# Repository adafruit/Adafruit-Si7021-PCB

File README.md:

## Adafruit Si7021 Temperature & Humidity Sensor Breakout PCB
<a href="http://www.adafruit.com/products/3251"><br/>
Click here to purchase one from the Adafruit shop</a>

It's summer and you're sweating and your hair's all frizzy and all you really want to know is why the weatherman said this morning that today's relative humidity would max out at a perfectly reasonable 42% when it feels more like 77%. Enter the Si7021 Temperature + Humidity Sensor - the best way to prove the weatherman wrong!

This lovely sensor for Silicon labs has ± 3% relative humidity measurements with a range of 0–80% RH, and ±0.4 °C temperature accuracy at a range of -10 to +85 °C. Great for all of your environmental sensing projects. It uses I2C for data transfer so it works with a wide range of microcontrollers.

To get you going fast, we spun up a custom made PCB in the STEMMA QT form factor, making them easy to interface with. The STEMMA QT connectors on either side are compatible with the SparkFun Qwiic I2C connectors. This allows you to make solderless connections between your development board and the LIS331s or to chain them with a wide range of other sensors and accessories using a compatible cable. We’ve of course broken out all the pins to standard headers and added a voltage regulator and level shifting so allow you to use it with either 3.3V or 5V systems such as the Raspberry Pi + Feather series or Arduino Uno respectively.

PCB files for the Adafruit Si7021 PCB. The format is EagleCAD schematic and board layout
- https://www.adafruit.com/products/3251

### License

Adafruit invests time and resources providing this open source design, please support Adafruit and open-source hardware by purchasing products from [Adafruit](https://www.adafruit.com)!

All text above must be included in any redistribution

Designed by Limor Fried/Ladyada for Adafruit Industries.
Creative Commons Attribution/Share-Alike, all text above must be included in any redistribution. 
See license.txt for additional information.

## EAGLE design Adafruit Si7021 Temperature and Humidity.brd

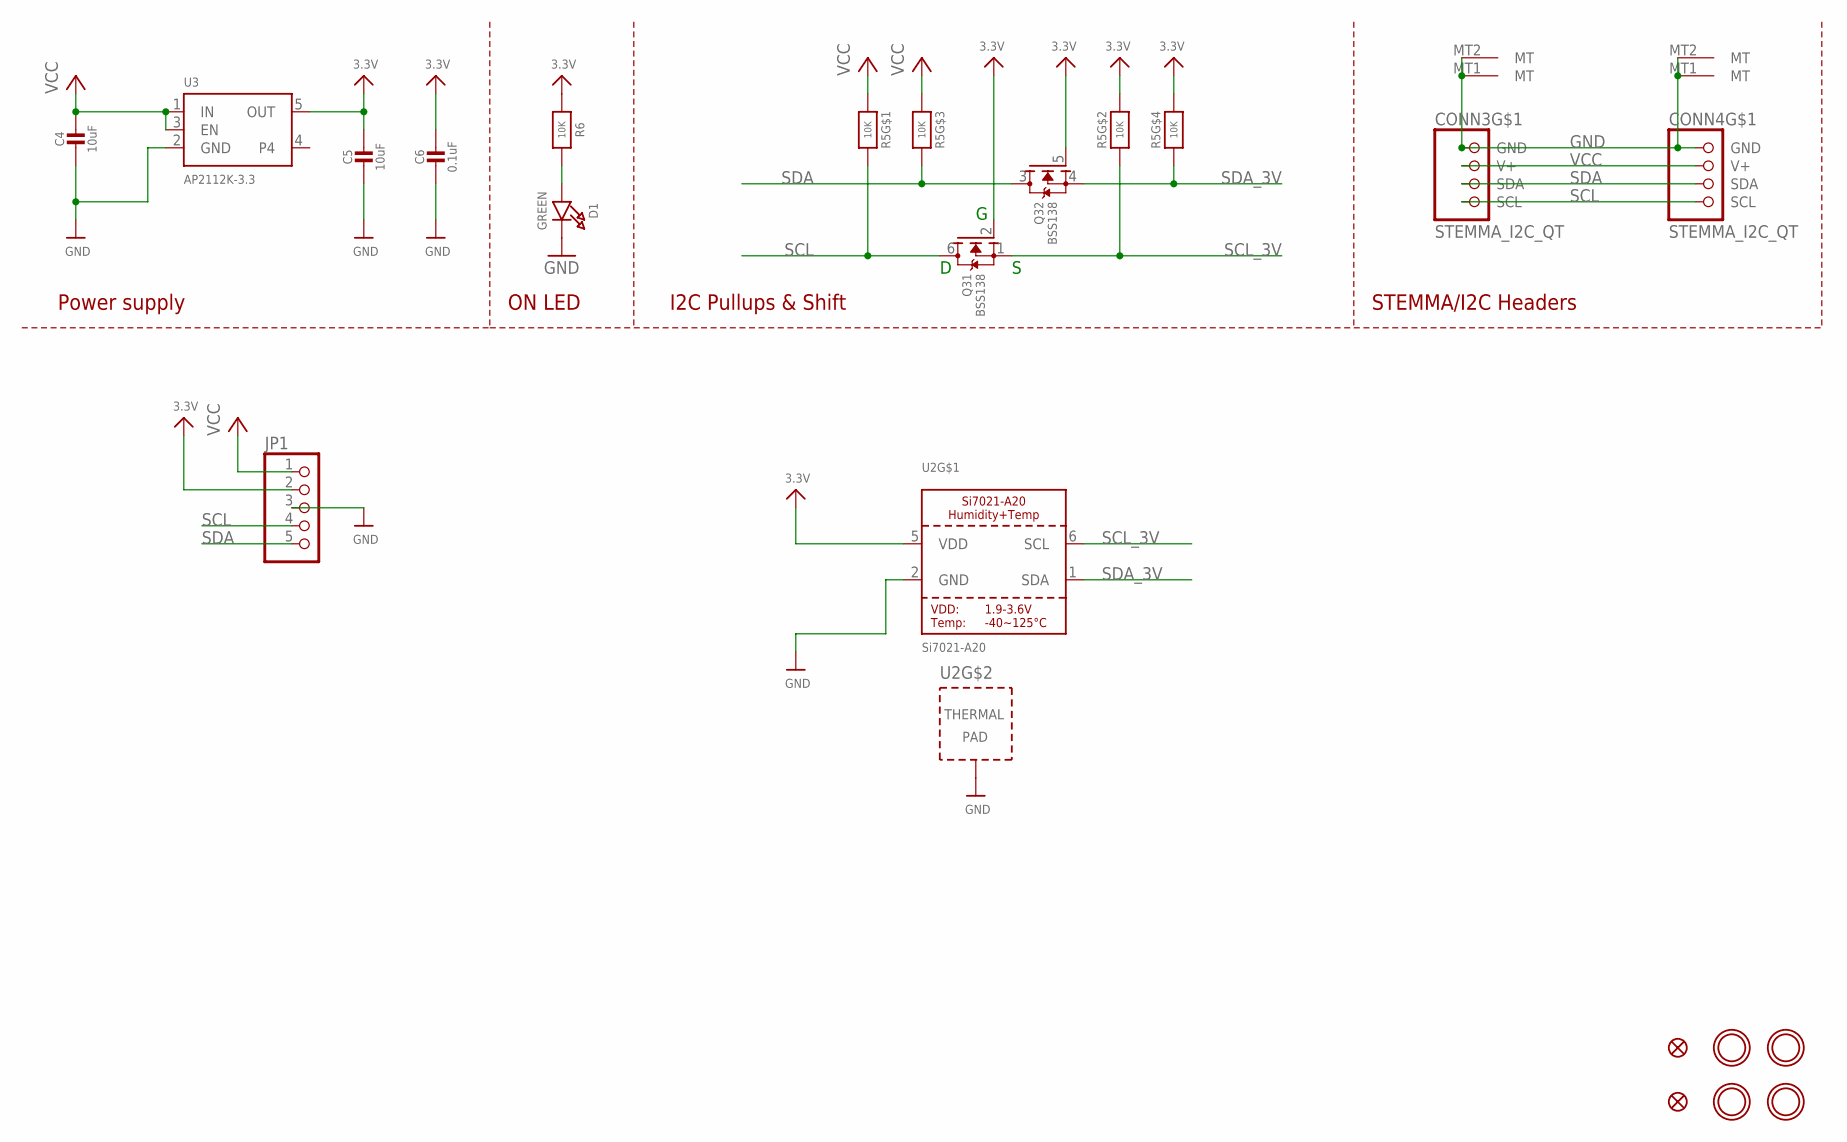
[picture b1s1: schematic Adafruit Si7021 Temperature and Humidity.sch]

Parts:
C4, C5: 10uF; 0805-NO
C6: 0.1uF; 0603-NO
CONN3, CONN4: STEMMA_I2C_QT; JST_SH4
D1: GREEN; CHIPLED_0603_NOOUTLINE
FID3, FID4: FIDUCIAL_1MM
JP1: HEADER-1X570MIL; 1X05_ROUND_70
Q3: BSS138; SOT363
R5: 10K; RESPACK_4X0603
R6: 10K; 0603-NO
U2: Si7021-A20; DFN6_3X3_SI
U3: AP2112K-3.3; SOT23-5
U$19, U$20, U$22, U$25: MOUNTINGHOLE2.5; MOUNTINGHOLE_2.5_PLATED

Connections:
3.3V: C5.1, C6.1, JP1.2, Q3.2 (G), Q3.5 (G), R5.2 (1), R5.4 (1), R6.1, U2.5 (VDD), U3.5 (OUT)
GND: C4.2, C5.2, C6.2, CONN3.1 (GND), CONN3.MT1 (MT), CONN3.MT2 (MT), CONN4.1 (GND), CONN4.MT1 (MT), CONN4.MT2 (MT), D1.C, JP1.3, U2.2 (GND), U2.PAD (TP), U3.2 (GND)
unnamed: D1.A, R6.2
SCL: CONN3.4 (SCL), CONN4.4 (SCL), JP1.4, Q3.6 (D), R5.8 (2)
SCL_3V: Q3.1 (S), R5.7 (2), U2.6 (SCL)
SDA: CONN3.3 (SDA), CONN4.3 (SDA), JP1.5, Q3.3 (D), R5.6 (2)
SDA_3V: Q3.4 (S), R5.5 (2), U2.1 (SDA)
VCC: C4.1, CONN3.2 (V+), CONN4.2 (V+), JP1.1, R5.1, R5.3 (1), U3.1 (IN), U3.3 (EN)

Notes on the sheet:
I2C Pullups & Shift
STEMMA/I2C Headers
ON LED
Power supply

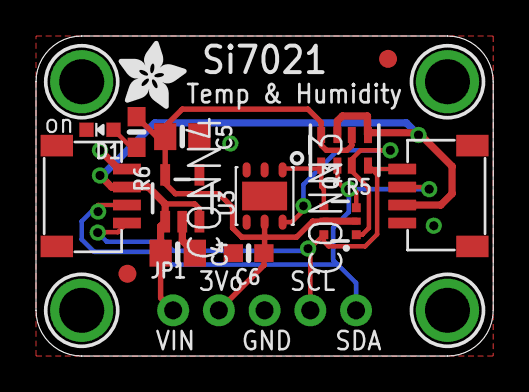
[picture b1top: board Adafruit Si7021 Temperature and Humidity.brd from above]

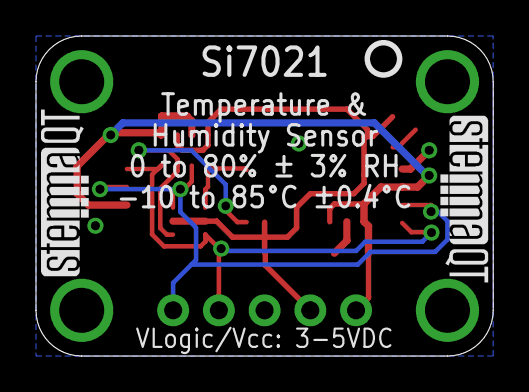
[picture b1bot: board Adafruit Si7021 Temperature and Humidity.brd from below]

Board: 2 copper layers, 25.4 x 17.8 mm, 22 parts (3 on the bottom side), 8 nets.

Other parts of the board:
U$28: ADAFRUIT_3.5MM
U$29: PCBFEAT-REV-040
U$30, U$31: STEMMAQT

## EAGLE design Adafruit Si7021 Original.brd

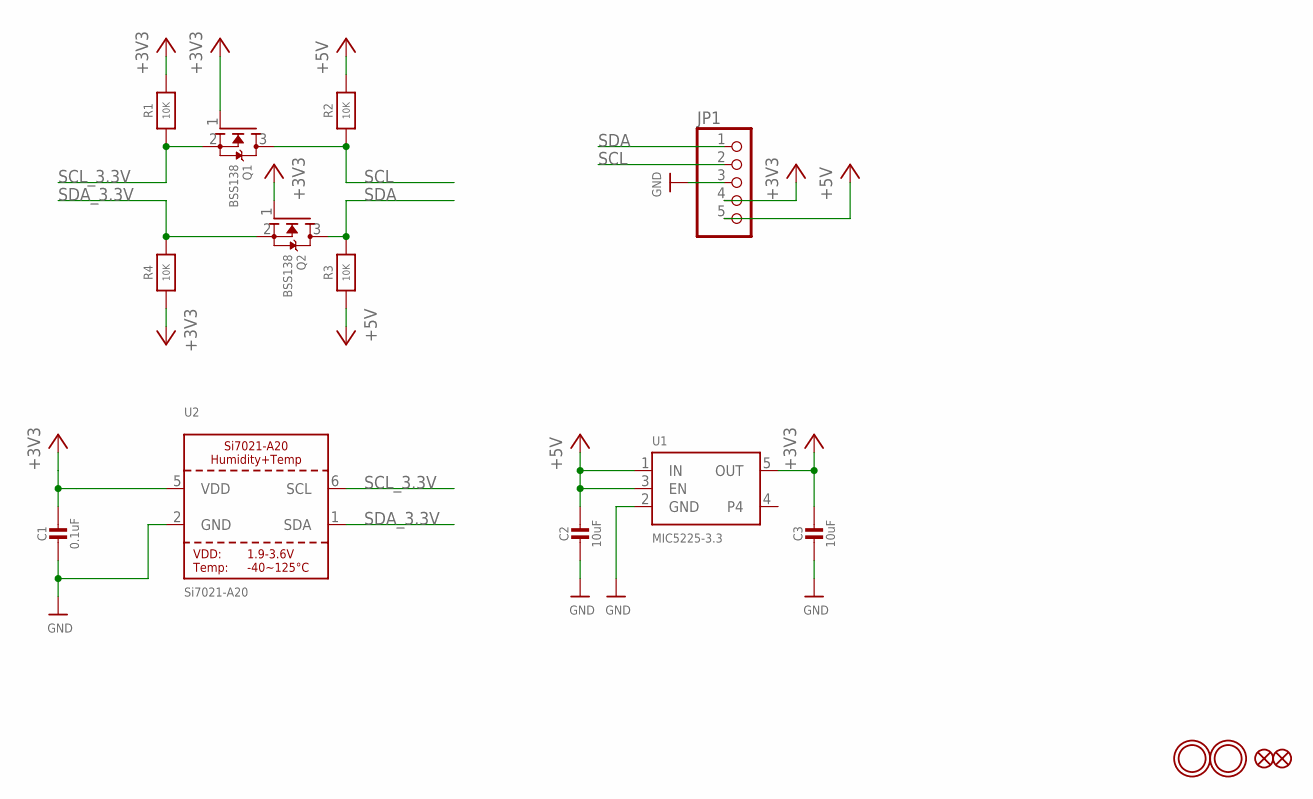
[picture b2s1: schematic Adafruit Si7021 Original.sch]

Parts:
C1: 0.1uF; 0805-NO
C2, C3: 10uF; 0805-NO
FID1, FID2: FIDUCIAL""; FIDUCIAL_1MM
JP1: HEADER-1X570MIL; 1X05_ROUND_70
Q1, Q2: BSS138; SOT23-WIDE
R1, R2, R3, R4: 10K; 0805-NO
U1: MIC5225-3.3; SOT23-5
U2: Si7021-A20; DFN6_3X3_SI
U$6, U$7: MOUNTINGHOLE2.5; MOUNTINGHOLE_2.5_PLATED

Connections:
+3V3: C1.1, C3.1, JP1.4, Q1.1 (G), Q2.1 (G), R1.2, R4.1, U1.5 (OUT), U2.5 (VDD)
GND: C1.2, C2.2, C3.2, JP1.3, U1.2 (GND), U2.2 (GND)
SCL: JP1.2, Q1.3 (D), R2.1
SCL_3.3V: Q1.2 (S), R1.1, U2.6 (SCL)
SDA: JP1.1, Q2.3 (D), R3.2
SDA_3.3V: Q2.2 (S), R4.2, U2.1 (SDA)
VIN: C2.1, JP1.5, R2.2, R3.1, U1.1 (IN), U1.3 (EN)

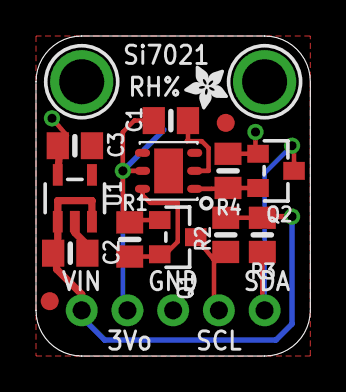
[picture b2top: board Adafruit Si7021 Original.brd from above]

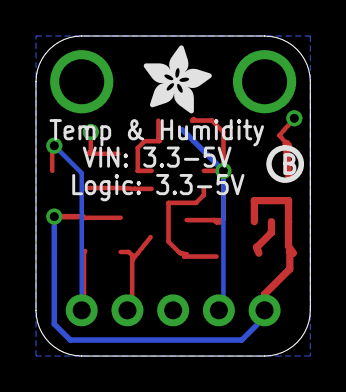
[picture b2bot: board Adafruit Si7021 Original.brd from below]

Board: 2 copper layers, 15.2 x 17.8 mm, 19 parts (2 on the bottom side), 7 nets.

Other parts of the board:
U$1: ADAFRUIT_2.5MM
U$9: PCBFEAT-REV-040
U$10: ADAFRUIT_3.5MM

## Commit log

2016-09-22 init
2020-08-27 Adding updated asset.
2020-08-27 Rename file.
2020-08-27 Add new board files.

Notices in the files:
parts and their libraries:
microbuilder: This work is placed in the public domain, and may be freely used for commercial and non-commercial work with the following conditions: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
